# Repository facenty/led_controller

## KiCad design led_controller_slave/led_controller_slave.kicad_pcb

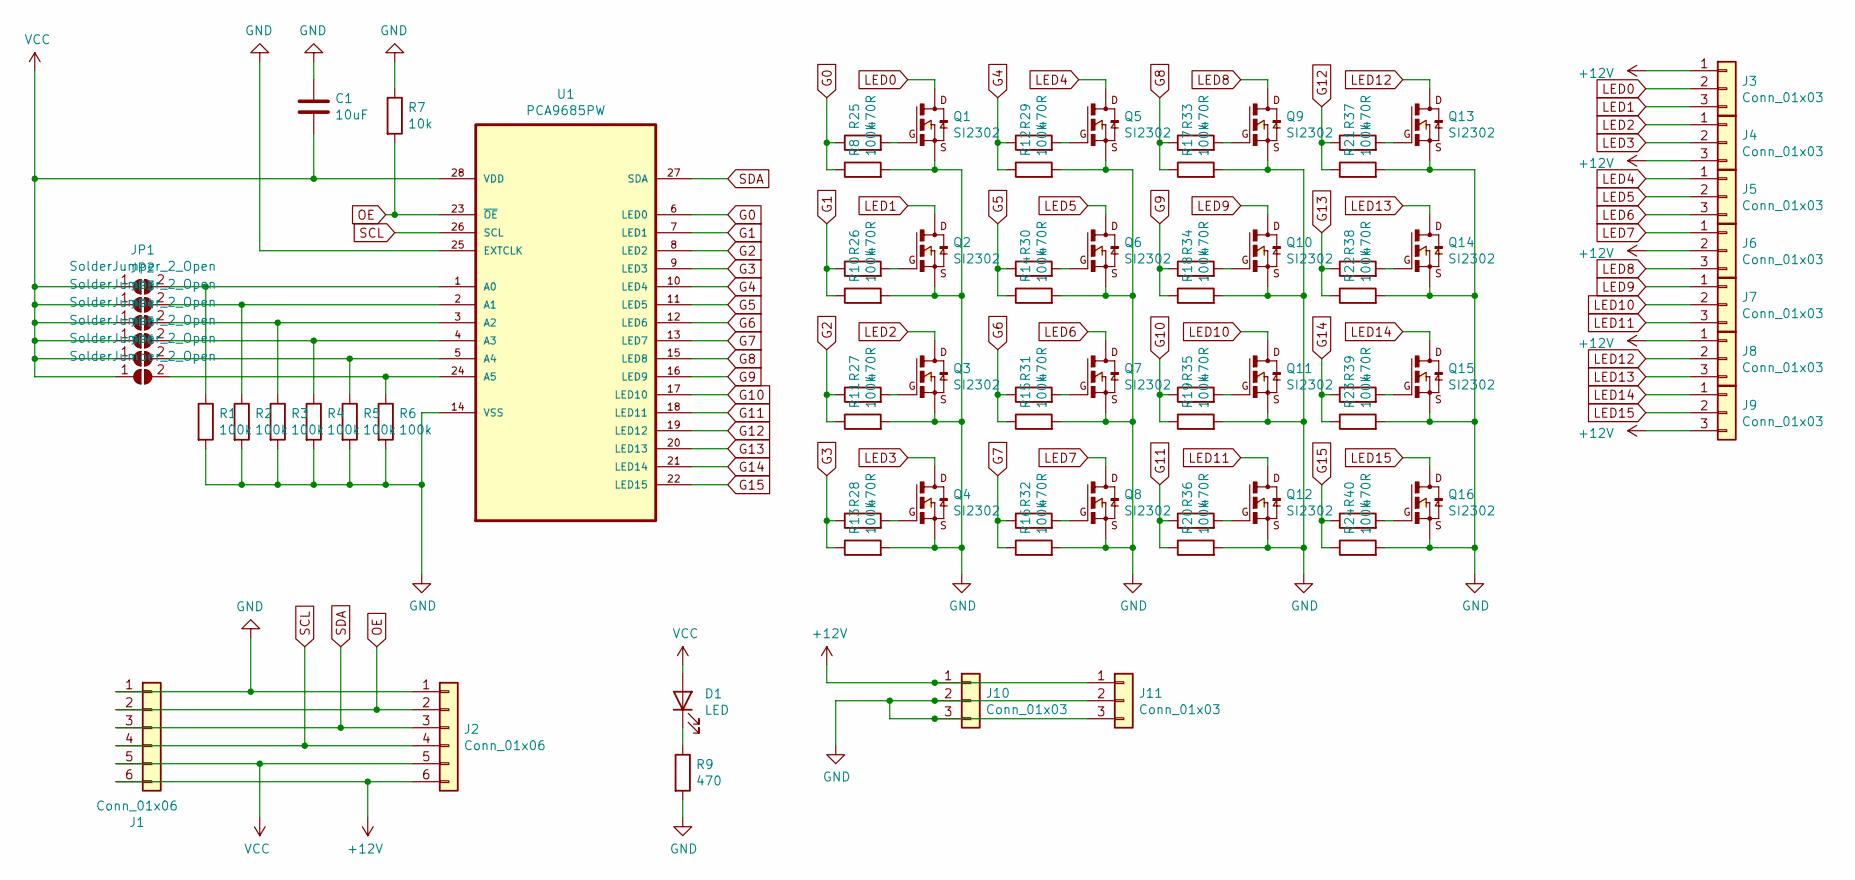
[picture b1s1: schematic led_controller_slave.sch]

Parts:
C1: 10uF; C_0603_1608Metric_Pad1.08x0.95mm_HandSolder
D1: LED; LED_0603_1608Metric_Pad1.05x0.95mm_HandSolder
J1, J2: Conn_01x06; PinHeader_1x06_P2.54mm_Vertical
J3, J4, J5, J6, J7, J8, J9: Conn_01x03; TerminalBlock_Altech_AK300-3_P5.00mm
J10, J11: Conn_01x03; BarrelJack_Horizontal
JP1, JP2, JP3, JP4, JP5, JP6: SolderJumper_2_Open; SolderJumper-2_P1.3mm_Open_RoundedPad1.0x1.5mm
Q1, Q2, Q3, Q4, Q5, Q6, Q7, Q8, Q9, Q10, Q11, Q12, Q13, Q14, Q15, Q16: SI2302; SOT23
R1, R2, R3, R4, R5, R6, R8, R10, R11, R12, R13, R14, R15, R16, R17, R18, R19, R20, R21, R22, R23, R24: 100k; R_0805_2012Metric_Pad1.20x1.40mm_HandSolder
R7: 10k; R_0805_2012Metric_Pad1.20x1.40mm_HandSolder
R9: 470; R_0805_2012Metric_Pad1.20x1.40mm_HandSolder
R25, R26, R27, R28, R29, R30, R31, R32, R33, R34, R35, R36, R37, R38, R39, R40: 470R; R_0805_2012Metric_Pad1.20x1.40mm_HandSolder
U1: PCA9685PW; SOP65P640X110-28N; MPN PCA9685PW

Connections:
+12V: J1.6, J2.6, J3.1, J4.3, J6.2, J8.1, J9.3, J10.1, J11.1
G0: R8.1, R25.1, U1.6 (LED0)
G1: R10.1, R26.1, U1.7 (LED1)
G2: R11.1, R27.1, U1.8 (LED2)
G3: R13.1, R28.1, U1.9 (LED3)
G4: R12.1, R29.1, U1.10 (LED4)
G5: R14.1, R30.1, U1.11 (LED5)
G6: R15.1, R31.1, U1.12 (LED6)
G7: R16.1, R32.1, U1.13 (LED7)
G8: R17.1, R33.1, U1.15 (LED8)
G9: R18.1, R34.1, U1.16 (LED9)
G10: R19.1, R35.1, U1.17 (LED10)
G11: R20.1, R36.1, U1.18 (LED11)
G12: R21.1, R37.1, U1.19 (LED12)
G13: R22.1, R38.1, U1.20 (LED13)
G14: R23.1, R39.1, U1.21 (LED14)
G15: R24.1, R40.1, U1.22 (LED15)
GND: C1.1, J1.1, J2.1, J10.2, J10.3, J11.2, J11.3, Q1.2, Q2.2, Q3.2, Q4.2, Q5.2, Q6.2, Q7.2, Q8.2, Q9.2, Q10.2, Q11.2, Q12.2, Q13.2, Q14.2, Q15.2, Q16.2, R1.2, R2.2, R3.2, R4.2, R5.2, R6.2, R7.1, R8.2, R9.2, R10.2, R11.2, R12.2, R13.2, R14.2, R15.2, R16.2, R17.2, R18.2, R19.2, R20.2, R21.2, R22.2, R23.2, R24.2, U1.14 (VSS), U1.25 (EXTCLK)
LED0: J3.2, Q1.3
LED1: J3.3, Q2.3
LED2: J4.1, Q3.3
LED3: J4.2, Q4.3
LED4: J5.1, Q5.3
LED5: J5.2, Q6.3
LED6: J5.3, Q7.3
LED7: J6.1, Q8.3
LED8: J6.3, Q9.3
LED9: J7.1, Q10.3
LED10: J7.2, Q11.3
LED11: J7.3, Q12.3
LED12: J8.2, Q13.3
LED13: J8.3, Q14.3
LED14: J9.1, Q15.3
LED15: J9.2, Q16.3
unnamed: D1.1 (K), R9.1
unnamed: JP1.2 (B), R1.1, U1.1 (A0)
unnamed: JP2.2 (B), R2.1, U1.2 (A1)
unnamed: JP3.2 (B), R3.1, U1.3 (A2)
unnamed: JP4.2 (B), R4.1, U1.4 (A3)
unnamed: JP5.2 (B), R5.1, U1.5 (A4)
unnamed: JP6.2 (B), R6.1, U1.24 (A5)
unnamed: Q1.1, R25.2
unnamed: Q2.1, R26.2
unnamed: Q3.1, R27.2
unnamed: Q4.1, R28.2
unnamed: Q5.1, R29.2
unnamed: Q6.1, R30.2
unnamed: Q7.1, R31.2
unnamed: Q8.1, R32.2
unnamed: Q9.1, R33.2
unnamed: Q10.1, R34.2
unnamed: Q11.1, R35.2
unnamed: Q12.1, R36.2
unnamed: Q13.1, R37.2
unnamed: Q14.1, R38.2
unnamed: Q15.1, R39.2
unnamed: Q16.1, R40.2
OE: J1.2, J2.2, R7.2, U1.23 (~OE)
SCL: J1.4, J2.4, U1.26 (SCL)
SDA: J1.3, J2.3, U1.27 (SDA)
VCC: C1.2, D1.2 (A), J1.5, J2.5, JP1.1 (A), JP2.1 (A), JP3.1 (A), JP4.1 (A), JP5.1 (A), JP6.1 (A), U1.28 (VDD)

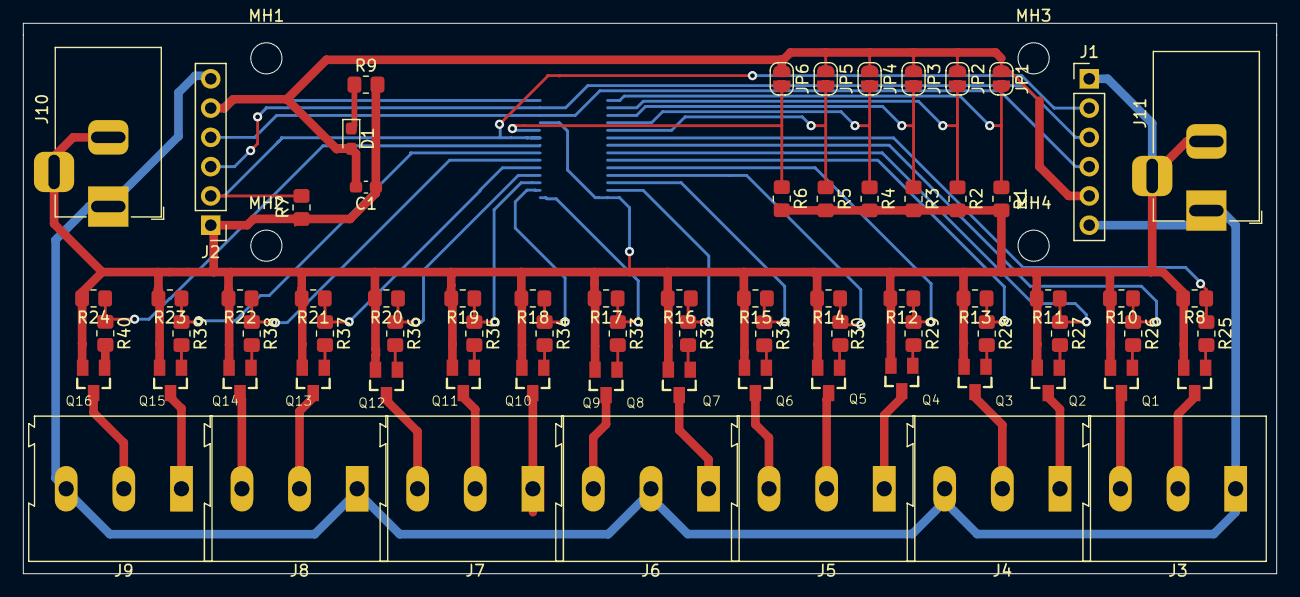
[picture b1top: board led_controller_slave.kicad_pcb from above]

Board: 2 copper layers, 108.7 x 47.7 mm, 80 parts (1 on the bottom side), 61 nets.

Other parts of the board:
MH1, MH2, MH3, MH4: MountingHole_2.7mm_M2.5

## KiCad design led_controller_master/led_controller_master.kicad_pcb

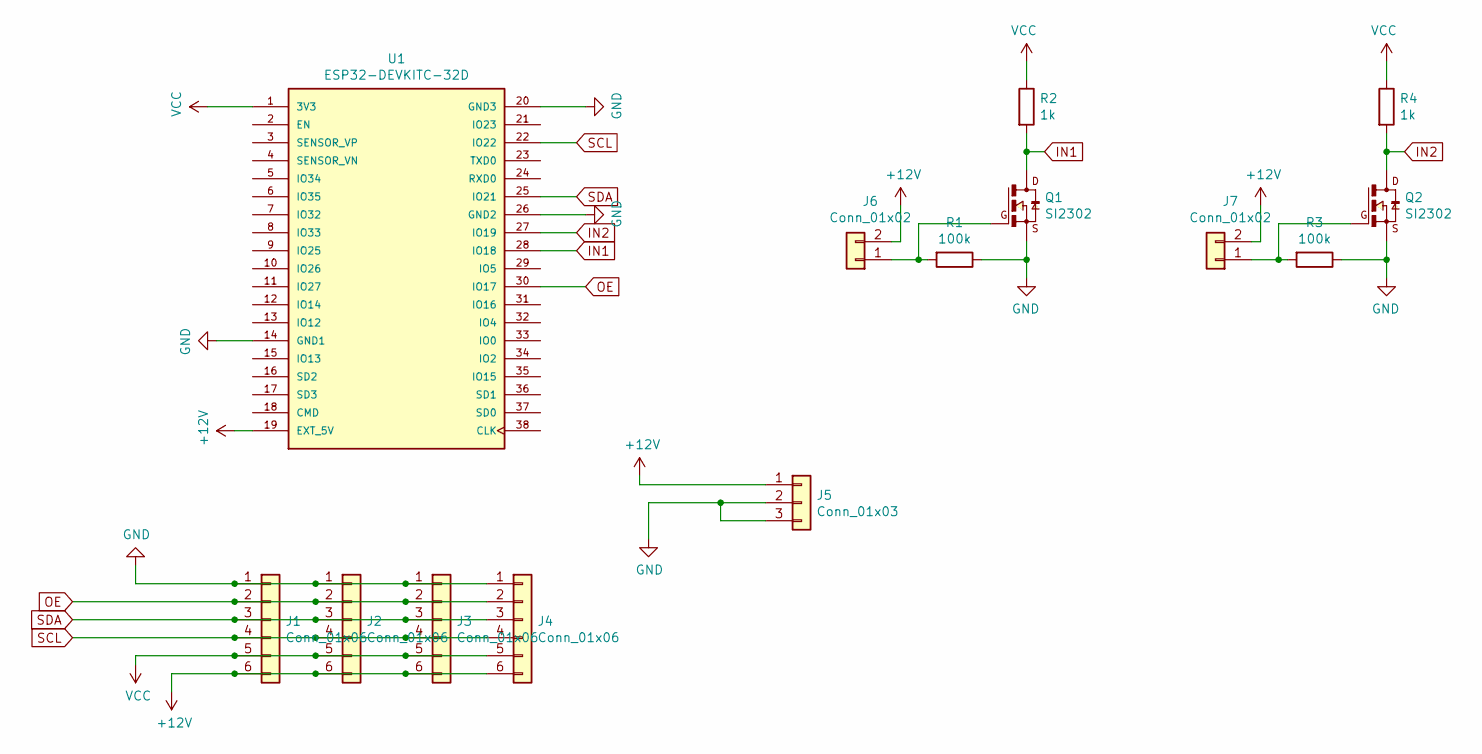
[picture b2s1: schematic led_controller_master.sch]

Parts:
J1, J2, J3, J4: Conn_01x06; PinHeader_1x06_P2.54mm_Vertical
J5: Conn_01x03; BarrelJack_Horizontal
J6, J7: Conn_01x02; TerminalBlock_Altech_AK300-2_P5.00mm
Q1, Q2: SI2302; SOT23
R1, R3: 100k; R_0603_1608Metric_Pad0.98x0.95mm_HandSolder
R2, R4: 1k; R_0603_1608Metric_Pad0.98x0.95mm_HandSolder
U1: ESP32-DEVKITC-32D; MODULE_ESP32-DEVKITC-32D; PARTREV 4

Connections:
+12V: J1.6, J2.6, J3.6, J4.6, J5.1, J6.2, J7.2, U1.19 (EXT_5V)
GND: J1.1, J2.1, J3.1, J4.1, J5.2, J5.3, Q1.2, Q2.2, R1.1, R3.1, U1.14 (GND1), U1.20 (GND3), U1.26 (GND2)
IN1: Q1.3, R2.2, U1.28 (IO18)
IN2: Q2.3, R4.2, U1.27 (IO19)
unnamed: J6.1, Q1.1, R1.2
unnamed: J7.1, Q2.1, R3.2
OE: J1.2, J2.2, J3.2, J4.2, U1.30 (IO17)
SCL: J1.4, J2.4, J3.4, J4.4, U1.22 (IO22)
SDA: J1.3, J2.3, J3.3, J4.3, U1.25 (IO21)
VCC: J1.5, J2.5, J3.5, J4.5, R2.1, R4.1, U1.1 (3V3)

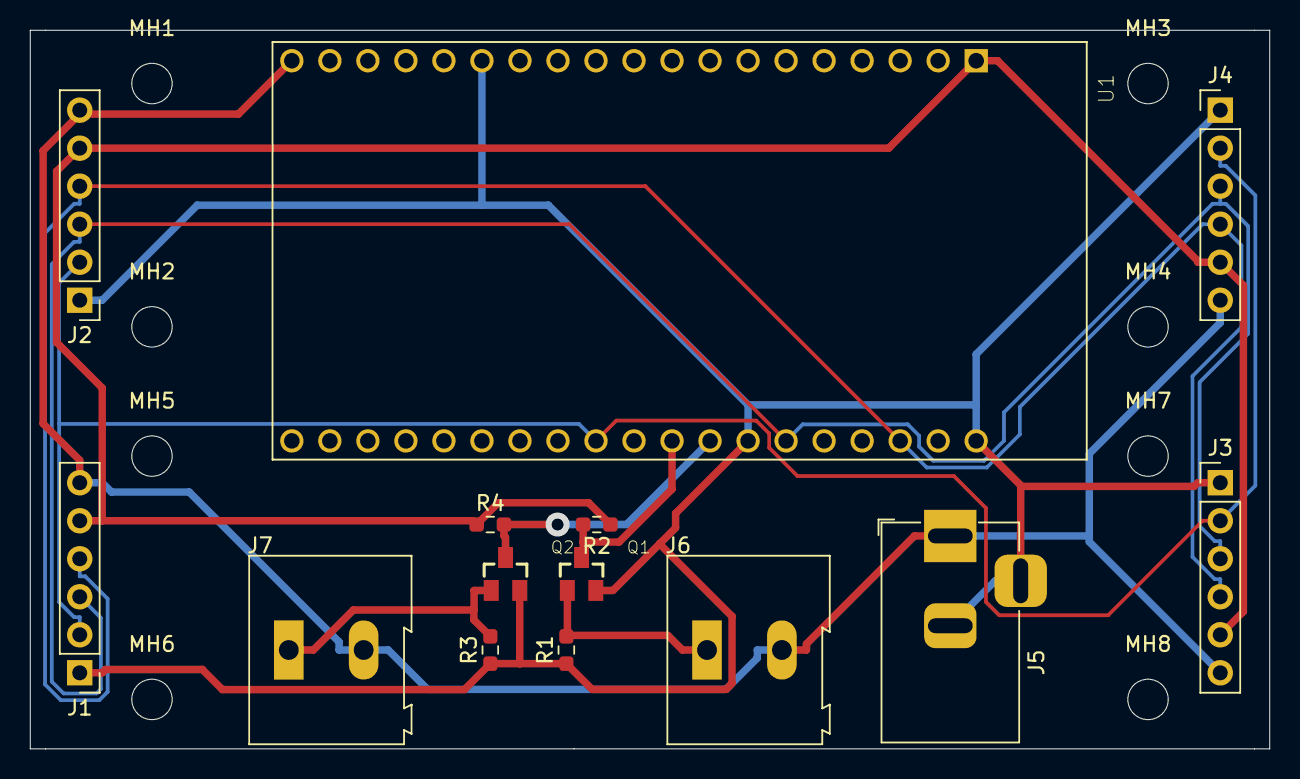
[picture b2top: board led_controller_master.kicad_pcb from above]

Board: 2 copper layers, 82.8 x 48.0 mm, 22 parts (0 on the bottom side), 10 nets.

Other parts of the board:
MH1, MH2, MH3, MH4, MH5, MH6, MH7, MH8: MountingHole_2.7mm_M2.5

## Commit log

2021-01-29 Create master and final fixes for slave
2021-02-01 POC - first stage of development
